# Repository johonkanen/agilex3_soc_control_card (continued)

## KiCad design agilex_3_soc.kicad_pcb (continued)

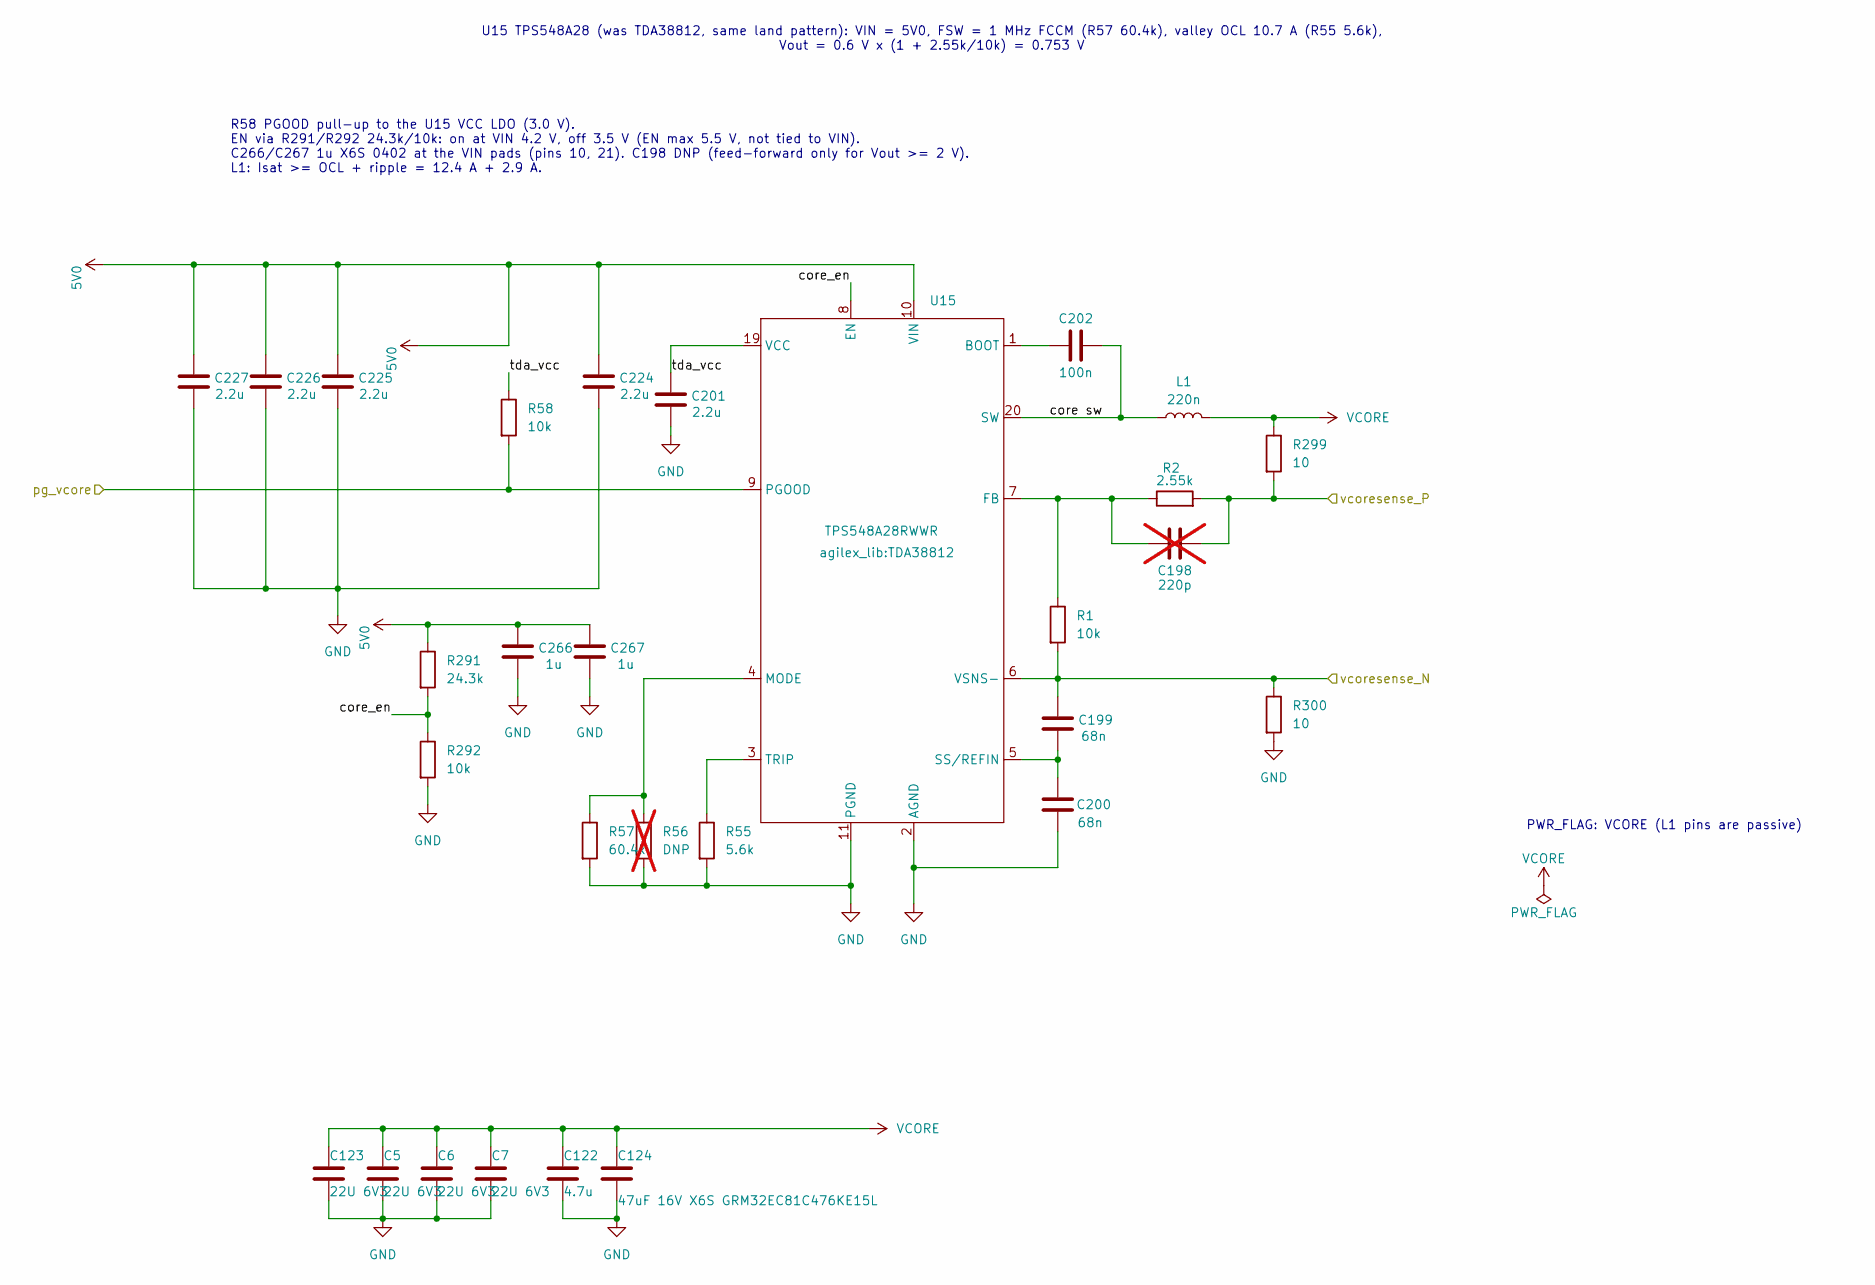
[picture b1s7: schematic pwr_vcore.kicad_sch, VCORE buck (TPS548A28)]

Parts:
C5, C6, C7, C123: 22U 6V3; C_0402_1005Metric; LCSC C415703
C122: 4.7u; C_0201_0603Metric; LCSC C5969171
C124: 47uF 16V X6S GRM32EC81C476KE15L; C_1210_3225Metric; LCSC C162512
C198: 220p; C_0402_1005Metric; LCSC C1530; not fitted
C199, C200: 68n; C_0402_1005Metric; LCSC C327019
C201, C224, C225, C226, C227: 2.2u; C_0402_1005Metric; LCSC C12530
C202: 100n; C_0402_1005Metric; LCSC C1525
C266, C267: 1u; C_0402_1005Metric; LCSC C393026
L1: 220n; L_TaiTech_TMPC0503H; LCSC C357176
R1, R58, R292: 10k; R_0402_1005Metric; LCSC C25744
R2: 2.55k; R_0402_1005Metric; LCSC C95596
R55: 5.6k; R_0402_1005Metric; LCSC C25908
R56: DNP; R_0402_1005Metric; not fitted
R57: 60.4k; R_0402_1005Metric; LCSC C25911
R291: 24.3k; R_0402_1005Metric; LCSC C26969
R299, R300: 10; R_0402_1005Metric; LCSC C25077
U15: TPS548A28RWWR; TDA38812; LCSC C5219375

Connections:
5V0: C224.2, C225.2, C226.2, C227.2, C266.2, C267.2, R291.1, U15.10 (VIN); also elsewhere on the board
/pwr_rails/EN: R58.2, U15.9 (PGOOD); also elsewhere on the board
/pwr_vcore/core sw: C202.2, L1.1, U15.20 (SW)
/pwr_vcore/core_en: R291.2, R292.1, U15.8 (EN)
/pwr_vcore/tda_vcc: C201.2, R58.1, U15.19 (VCC)
/pwr_vcore/vcoresense_N: C199.2, R1.2, R300.1, U15.6 (VSNS-); also elsewhere on the board
/soc_power/vcoresense_P: C198.2, R2.2, R299.2; also elsewhere on the board
GND: C5.2, C6.2, C7.2, C122.2, C123.2, C124.2, C200.1, C201.1, C224.1, C225.1, C226.1, C227.1, C266.1, C267.1, R55.2, R56.2, R57.2, R292.2, R300.2, U15.2 (AGND), U15.11 (PGND); also elsewhere on the board
unnamed: C202.1, U15.1 (BOOT)
unnamed: C198.1, R1.1, R2.1, U15.7 (FB)
unnamed: R56.1, R57.1, U15.4 (MODE)
unnamed: C199.1, C200.2, U15.5 (SS/REFIN)
unnamed: R55.1, U15.3 (TRIP)
VCORE: C5.1, C6.1, C7.1, C122.1, C123.1, C124.1, L1.2, R299.1; also elsewhere on the board

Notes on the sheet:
U15 TPS548A28 (was TDA38812, same land pattern): VIN = 5V0, FSW = 1 MHz FCCM (R57 60.4k), valley OCL 10.7 A (R55 5.6k), Vout = 0.6 V x (1 + 2.55k/10k) = 0.753 V
R58 PGOOD pull-up to the U15 VCC LDO (3.0 V). EN via R291/R292 24.3k/10k: on at VIN 4.2 V, off 3.5 V (EN max 5.5 V, not tied to VIN). C266/C267 1u X6S 0402 at the VIN pads (pins 10, 21). C198 DNP (feed-forward only for Vout >= 2 V). L1: Isat >= OCL + ripple = 12.4 A + 2.9 A.
PWR_FLAG: VCORE (L1 pins are passive)

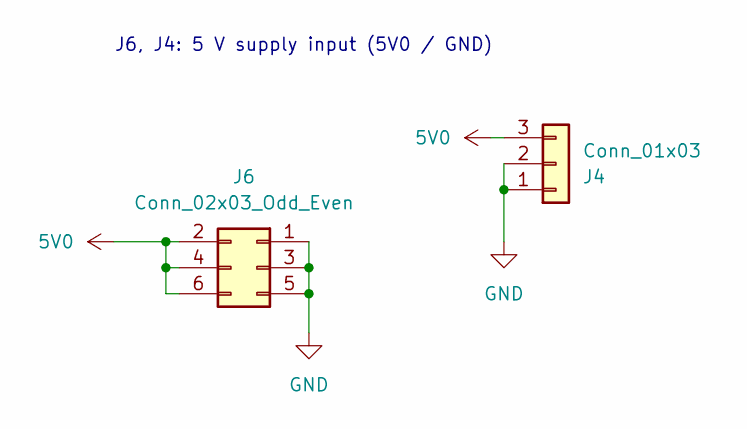
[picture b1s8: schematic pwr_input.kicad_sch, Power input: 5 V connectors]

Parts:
J4: Conn_01x03; PinHeader_1x03_P2.54mm_Vertical; LCSC C2937625
J6: Conn_02x03_Odd_Even; PinHeader_2x03_P1.27mm_Vertical; LCSC C22438118

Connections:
5V0: J4.3, J6.2, J6.4, J6.6; also elsewhere on the board
GND: J4.1, J4.2, J6.1, J6.3, J6.5; also elsewhere on the board

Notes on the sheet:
J6, J4: 5 V supply input (5V0 / GND)

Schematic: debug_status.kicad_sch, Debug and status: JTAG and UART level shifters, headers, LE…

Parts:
C253, C254, C273, C274: 100n; C_0402_1005Metric; LCSC C1525
D1, D2: KT-0603R; LED_0603_1608Metric; LCSC C2286
J1: Conn_01x05; PinHeader_1x05_P2.54mm_Vertical; LCSC C492404
J2: Conn_01x03; PinHeader_1x03_P2.54mm_Vertical; LCSC C2937625
J10: HPS_UART_3V3; PinHeader_1x02_P2.54mm_Vertical; LCSC C492401
R16, R17: 680R; R_0402_1005Metric; LCSC C25130
R47, R48: 10k; R_0402_1005Metric; LCSC C25744
R301: 4K7; R_0402_1005Metric; LCSC C25900
U1, U42: SN74AXC4T774PWR; TSSOP-16_4.4x5mm_P0.65mm; LCSC C1849453

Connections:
1V8: C253.1, C273.1, U1.15 (VCCB), U42.15 (VCCB); also elsewhere on the board
3V3: C254.1, C274.1, R47.1, R48.1, R301.1, U1.1 (DIR1), U1.2 (DIR2), U1.7 (DIR3), U1.16 (VCCA), U42.2 (DIR2), U42.16 (VCCA); also elsewhere on the board
/debug_status/hps_uart0_rx_3v3: J10.2, R301.2, U42.4 (A2)
/debug_status/hps_uart0_tx_3v3: J10.1, U42.3 (A1)
/debug_status/jtag_tck_3v3: J1.2, U1.4 (A2)
/debug_status/jtag_tdi_3v3: J1.1, U1.3 (A1)
/debug_status/jtag_tdo_3v3: J1.4, U1.6 (A4)
/debug_status/jtag_tms_3v3: J1.3, U1.5 (A3)
/debug_status/pg_all_3v3: R16.2, U42.6 (A4)
/eth_rst_n: U42.12 (B3); also elsewhere on the board
/fpga_bank6ab/iob6b8: J2.2, R47.2; also elsewhere on the board
/fpga_bank6ab/iob6b11: J2.1, R48.2; also elsewhere on the board
/fpga_led: R17.2; also elsewhere on the board
/hps_uart0_rx: U42.13 (B2); also elsewhere on the board
/hps_uart0_tx: U42.14 (B1); also elsewhere on the board
/pg_all: U42.11 (B4); also elsewhere on the board
/phy_rst_n: U42.5 (A3); also elsewhere on the board
/tck: U1.13 (B2); also elsewhere on the board
/tdi: U1.14 (B1); also elsewhere on the board
/tdo: U1.11 (B4); also elsewhere on the board
/tms: U1.12 (B3); also elsewhere on the board
GND: C253.2, C254.2, C273.2, C274.2, D1.1 (K), D2.1 (K), J1.5, J2.3, U1.8 (DIR4), U1.9 (OE), U1.10 (GND), U42.1 (DIR1), U42.7 (DIR3), U42.8 (DIR4), U42.9 (OE), U42.10 (GND); also elsewhere on the board
unnamed: D1.2 (A), R16.1
unnamed: D2.2 (A), R17.1

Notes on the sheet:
U42 SN74AXC4T774, 1.8 V (B) <-> 3.3 V (A): Ch1 DIR1 low = B->A: HPS UART0 TX out Ch2 DIR2 high = A->B: UART0 RX in Ch3: eth_rst_n -> phy_rst_n (PHY reset) Ch4 DIR4 low: pg_all (1.8 V) -> pg_all_3v3 -> LED D1
D2: user LED on FPGA IO CE6 (bank 6B, 3.3 V)
D1: power good (pg_all_3v3, from U42 ch4)
pg_all: regulator power-good wired-AND (ps1); also the PHY RESET_N pull-up (eth)
J10: 1 = TX (3.3 V out), 2 = RX (3.3 V in). GND on J2.3 / J4
UART RX idle pull-up (A2-03): U42 has 71k pull-downs, so RX reads as a break with no cable on J10.

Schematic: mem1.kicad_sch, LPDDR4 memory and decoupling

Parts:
C44, C47, C48: 22U 6V3; C_0402_1005Metric; LCSC C415703
C49, C50, C52, C53, C54, C56, C57, C58, C60, C61, C62, C63, C65, C66, C67, C69, C70, C71, C73, C74, C75, C77, C78, C79, C81, C82, C83, C85, C87, C89, C93: 100N; C_0201_0603Metric; LCSC C190183
C262, C263, C264, C265: 1u; C_0402_1005Metric; LCSC C52923
R43: 240R; R_0402_1005Metric; LCSC C25094
R44: 1K0; R_0402_1005Metric; LCSC C11702
U12: H9HCNNN8KUMLHR-NMO; BGA-200_10x15mm_Layout12x22_P0.8x0.65mm; LCSC C51891855

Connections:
1V1: C47.1, C49.1, C50.1, C53.1, C54.1, C57.1, C58.1, C61.1, C62.1, C63.1, C65.1, C66.1, C67.1, C69.1, C70.1, C71.1, C73.1, C74.1, C75.1, C77.1, C78.1, C79.1, C81.1, C82.1, C83.1, C85.1, C87.1, C89.1, C93.1, C262.1, C263.1, C264.1, C265.1, R43.2, U12.A4 (VDD2), U12.A9 (VDD2), U12.AA3 (VDDQ), U12.AA5 (VDDQ), U12.AA8 (VDDQ), U12.AA10 (VDDQ), U12.AB4 (VDD2), U12.AB9 (VDD2), U12.B3 (VDDQ), U12.B5 (VDDQ), U12.B8 (VDDQ), U12.B10 (VDDQ), U12.D1 (VDDQ), U12.D5 (VDDQ), U12.D8 (VDDQ), U12.D12 (VDDQ), U12.F3 (VDDQ), U12.F5 (VDD2), U12.F8 (VDD2), U12.F10 (VDDQ), U12.G2 (ODT_CA_A), U12.H1 (VDD2), U12.H5 (VDD2), U12.H8 (VDD2), U12.H12 (VDD2), U12.K1 (VDD2), U12.K3 (VDD2), U12.K10 (VDD2), U12.K12 (VDD2), U12.N1 (VDD2), U12.N3 (VDD2), U12.N10 (VDD2), U12.N12 (VDD2), U12.R1 (VDD2), U12.R5 (VDD2), U12.R8 (VDD2), U12.R12 (VDD2), U12.T2 (ODT_CA_B), U12.U3 (VDDQ), U12.U5 (VDD2), U12.U8 (VDD2), U12.U10 (VDDQ), U12.W1 (VDDQ), U12.W5 (VDDQ), U12.W8 (VDDQ), U12.W12 (VDDQ); also elsewhere on the board
1V8: C44.1, C48.1, C52.1, C56.1, C60.1, U12.F1 (VDD1), U12.F12 (VDD1), U12.G4 (VDD1), U12.G9 (VDD1), U12.T4 (VDD1), U12.T9 (VDD1), U12.U1 (VDD1), U12.U12 (VDD1); also elsewhere on the board
/IOBANK 3/ca0: U12.H2 (CA0_A), U12.R2 (CA0_B); also elsewhere on the board
/IOBANK 3/ca1: U12.J2 (CA1_A), U12.P2 (CA1_B); also elsewhere on the board
/IOBANK 3/ca2: U12.H9 (CA2_A), U12.R9 (CA2_B); also elsewhere on the board
/IOBANK 3/ca3: U12.H10 (CA3_A), U12.R10 (CA3_B); also elsewhere on the board
/IOBANK 3/ca4: U12.H11 (CA4_A), U12.R11 (CA4_B); also elsewhere on the board
/IOBANK 3/ca5: U12.J11 (CA5_A), U12.P11 (CA5_B); also elsewhere on the board
/IOBANK 3/ck_N: U12.J9 (CK_C_A), U12.P9 (CK_C_B); also elsewhere on the board
/IOBANK 3/ck_P: U12.J8 (CK_T_A), U12.P8 (CK_T_B); also elsewhere on the board
/IOBANK 3/cke: U12.J4 (CKE0_A), U12.P4 (CKE0_B); also elsewhere on the board
/IOBANK 3/dm0: U12.C3 (DMI0_A); also elsewhere on the board
/IOBANK 3/dm1: U12.C10 (DMI1_A); also elsewhere on the board
/IOBANK 3/dm2: U12.Y3 (DMI0_B); also elsewhere on the board
/IOBANK 3/dm3: U12.Y10 (DMI1_B); also elsewhere on the board
/IOBANK 3/dq0: U12.B2 (DQ0_A); also elsewhere on the board
/IOBANK 3/dq1: U12.C2 (DQ1_A); also elsewhere on the board
/IOBANK 3/dq2: U12.E2 (DQ2_A); also elsewhere on the board
/IOBANK 3/dq3: U12.F2 (DQ3_A); also elsewhere on the board
/IOBANK 3/dq4: U12.F4 (DQ4_A); also elsewhere on the board
/IOBANK 3/dq5: U12.E4 (DQ5_A); also elsewhere on the board
/IOBANK 3/dq6: U12.C4 (DQ6_A); also elsewhere on the board
/IOBANK 3/dq7: U12.B4 (DQ7_A); also elsewhere on the board
/IOBANK 3/dq8: U12.B11 (DQ8_A); also elsewhere on the board
/IOBANK 3/dq9: U12.C11 (DQ9_A); also elsewhere on the board
/IOBANK 3/dq10: U12.E11 (DQ10_A); also elsewhere on the board
/IOBANK 3/dq11: U12.F11 (DQ11_A); also elsewhere on the board
/IOBANK 3/dq12: U12.F9 (DQ12_A); also elsewhere on the board
/IOBANK 3/dq13: U12.E9 (DQ13_A); also elsewhere on the board
/IOBANK 3/dq14: U12.C9 (DQ14_A); also elsewhere on the board
/IOBANK 3/dq15: U12.B9 (DQ15_A); also elsewhere on the board
/IOBANK 3/dq16: U12.AA2 (DQ0_B); also elsewhere on the board
/IOBANK 3/dq17: U12.Y2 (DQ1_B); also elsewhere on the board
/IOBANK 3/dq18: U12.V2 (DQ2_B); also elsewhere on the board
/IOBANK 3/dq19: U12.U2 (DQ3_B); also elsewhere on the board
/IOBANK 3/dq20: U12.U4 (DQ4_B); also elsewhere on the board
/IOBANK 3/dq21: U12.V4 (DQ5_B); also elsewhere on the board
/IOBANK 3/dq22: U12.Y4 (DQ6_B); also elsewhere on the board
/IOBANK 3/dq23: U12.AA4 (DQ7_B); also elsewhere on the board
/IOBANK 3/dq24: U12.AA11 (DQ8_B); also elsewhere on the board
/IOBANK 3/dq25: U12.Y11 (DQ9_B); also elsewhere on the board
/IOBANK 3/dq26: U12.V11 (DQ10_B); also elsewhere on the board
/IOBANK 3/dq27: U12.U11 (DQ11_B); also elsewhere on the board
/IOBANK 3/dq28: U12.U9 (DQ12_B); also elsewhere on the board
/IOBANK 3/dq29: U12.V9 (DQ13_B); also elsewhere on the board
/IOBANK 3/dq30: U12.Y9 (DQ14_B); also elsewhere on the board
/IOBANK 3/dq31: U12.AA9 (DQ15_B); also elsewhere on the board
/IOBANK 3/dqs0_N: U12.E3 (DQS0_C_A); also elsewhere on the board
/IOBANK 3/dqs0_P: U12.D3 (DQS0_T_A); also elsewhere on the board
/IOBANK 3/dqs1_N: U12.E10 (DQS1_C_A); also elsewhere on the board
/IOBANK 3/dqs1_P: U12.D10 (DQS1_T_A); also elsewhere on the board
/IOBANK 3/dqs2_N: U12.V3 (DQS0_C_B); also elsewhere on the board
/IOBANK 3/dqs2_P: U12.W3 (DQS0_T_B); also elsewhere on the board
/IOBANK 3/dqs3_N: U12.V10 (DQS1_C_B); also elsewhere on the board
/IOBANK 3/dqs3_P: U12.W10 (DQS1_T_B); also elsewhere on the board
/IOBANK 3/~cs: U12.H4 (CS0_A), U12.R4 (CS0_B); also elsewhere on the board
/IOBANK 3/~rst: R44.1, U12.T11 (RESET_N); also elsewhere on the board
GND: C44.2, C47.2, C48.2, C49.2, C50.2, C52.2, C53.2, C54.2, C56.2, C57.2, C58.2, C60.2, C61.2, C62.2, C63.2, C65.2, C66.2, C67.2, C69.2, C70.2, C71.2, C73.2, C74.2, C75.2, C77.2, C78.2, C79.2, C81.2, C82.2, C83.2, C85.2, C87.2, C89.2, C93.2, C262.2, C263.2, C264.2, C265.2, R44.2, U12.A3 (VSS), U12.A10 (VSS), U12.AB3 (VSS), U12.AB5 (VSS), U12.AB8 (VSS), U12.AB10 (VSS), U12.C1 (VSS), U12.C5 (VSS), U12.C8 (VSS), U12.C12 (VSS), U12.D2 (VSS), U12.D4 (VSS), U12.D9 (VSS), U12.D11 (VSS), U12.E1 (VSS), U12.E5 (VSS), U12.E8 (VSS), U12.E12 (VSS), U12.G1 (VSS), U12.G3 (VSS), U12.G5 (VSS), U12.G8 (VSS), U12.G10 (VSS), U12.G12 (VSS), U12.J1 (VSS), U12.J3 (VSS), U12.J10 (VSS), U12.J12 (VSS), U12.K2 (VSS), U12.K4 (VSS), U12.K9 (VSS), U12.K11 (VSS), U12.N2 (VSS), U12.N4 (VSS), U12.N9 (VSS), U12.N11 (VSS), U12.P1 (VSS), U12.P3 (VSS), U12.P10 (VSS), U12.P12 (VSS), U12.T1 (VSS), U12.T3 (VSS), U12.T5 (VSS), U12.T8 (VSS), U12.T10 (VSS), U12.T12 (VSS), U12.V1 (VSS), U12.V5 (VSS), U12.V8 (VSS), U12.V12 (VSS), U12.W2 (VSS), U12.W4 (VSS), U12.W9 (VSS), U12.W11 (VSS), U12.Y1 (VSS), U12.Y5 (VSS), U12.Y8 (VSS), U12.Y12 (VSS); also elsewhere on the board
unnamed: R43.1, U12.A5 (ZQ0)

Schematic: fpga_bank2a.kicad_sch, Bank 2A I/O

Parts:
R24: 240R; R_0402_1005Metric; LCSC C25094
U7: A5EB013B-B23B; Altera_B23B

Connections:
/fpga_bank2a/rzq_b_2a: R24.1, U7.DP58 (2A_B_IO38_IOB_RZQ_B_2A_DIFF_IO_2A_B5p)
GND: R24.2; also elsewhere on the board

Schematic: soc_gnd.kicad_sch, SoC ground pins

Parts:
U7: A5EB013B-B23B; Altera_B23B

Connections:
/pwr_vcore/vcoresense_N: U7.BN44 (GNDSENSE); also elsewhere on the board
GND: U7.A3 (GND), U7.A5 (GND), U7.A17 (GND), U7.A28 (GND), U7.A41 (GND), U7.A53 (GND), U7.A63 (GND), U7.A73 (GND), U7.A74 (GND), U7.AA72 (GND), U7.AB27 (GND), U7.AB35 (GND), U7.AB42 (GND), U7.AB51 (GND), U7.AB59 (GND), U7.AB65 (GND), U7.AE4 (GND), U7.AE16 (GND), U7.AF2 (GND), U7.AF74 (GND), U7.AG34 (GND), U7.AG44 (GND), U7.AG49 (GND), U7.AG52 (GND), U7.AG54 (GND), U7.AG57 (GND), U7.AG60 (GND), U7.AH8 (GND), U7.AK64 (GND), U7.AK72 (GND), U7.AL23 (GND), U7.AL26 (GND), U7.AL40 (GND), U7.AL44 (GND), U7.AL49 (GND), U7.AL57 (GND), U7.AL60 (GND), U7.AM1 (GND), U7.AM75 (GND), U7.AN69 (GND), U7.AR29 (GND), U7.AR44 (GND), U7.AR46 (GND), U7.AR54 (GND), U7.AR60 (GND), U7.AT4 (GND), U7.AT16 (GND), U7.AV8 (GND), U7.AW26 (GND), U7.AW37 (GND), U7.AW44 (GND), U7.AW52 (GND), U7.AW54 (GND), U7.AW60 (GND), U7.AY64 (GND), U7.AY72 (GND), U7.B13 (GND), U7.B20 (GND), U7.B23 (GND), U7.B36 (GND), U7.B47 (GND), U7.B60 (GND), U7.B70 (GND), U7.B75 (GND), U7.BA2 (GND), U7.BA74 (GND), U7.BB23 (GND), U7.BB31 (GND), U7.BB40 (GND), U7.BB49 (GND), U7.BB57 (GND), U7.BB60 (GND), U7.BC69 (GND), U7.BE4 (GND), U7.BE16 (GND), U7.BF29 (GND), U7.BF37 (GND), U7.BF46 (GND), U7.BF54 (GND), U7.BF60 (GND), U7.BG1 (GND), U7.BG75 (GND), U7.BH8 (GND), U7.BJ34 (GND), U7.BJ44 (GND), U7.BJ52 (GND), U7.BJ57 (GND), U7.BK64 (GND), U7.BK72 (GND), U7.BM64 (GND), U7.BM67 (GND), U7.BM69 (GND), U7.BN23 (GND), U7.BN31 (GND), U7.BN40 (GND), U7.BN49 (GND), U7.BN57 (GND), U7.BR4 (GND), U7.BR16 (GND), U7.BT2 (GND), U7.BT74 (GND), U7.BU29 (GND), U7.BU37 (GND), U7.BU46 (GND), U7.BU54 (GND), U7.BU57 (GND), U7.BU60 (GND), U7.BV8 (GND), U7.BY64 (GND), U7.BY72 (GND), U7.C1 (GND), U7.C4 (GND), U7.C16 (GND), U7.C75 (GND), U7.CA26 (GND), U7.CA34 (GND), U7.CA44 (GND), U7.CA52 (GND), U7.CA60 (GND), U7.CB1 (GND), U7.CB75 (GND), U7.CC69 (GND), U7.CD31 (GND), U7.CD40 (GND), U7.CD49 (GND), U7.CD57 (GND), U7.CE4 (GND), U7.CE16 (GND), U7.CG29 (GND), U7.CG37 (GND), U7.CG46 (GND), U7.CG54 (GND), U7.CH8 (GND), U7.CK64 (GND), U7.CK72 (GND), U7.CL23 (GND), U7.CL26 (GND), U7.CL34 (GND), U7.CL44 (GND), U7.CL52 (GND), U7.CL60 (GND), U7.CM2 (GND), U7.CM74 (GND), U7.CN69 (GND), U7.CR4 (GND), U7.CR16 (GND), U7.CT31 (GND), U7.CT40 (GND), U7.CT49 (GND), U7.CT57 (GND), U7.CU1 (GND), U7.CU74 (GND), U7.CU75 (GND), U7.CV8 (GND), U7.CW29 (GND), U7.CW37 (GND), U7.CW46 (GND), U7.CW54 (GND), U7.CY64 (GND), U7.CY72 (GND), U7.D72 (GND), U7.DE2 (GND), U7.DE74 (GND), U7.DF9 (GND), U7.DF18 (GND), U7.DF24 (GND), U7.DF32 (GND), U7.DF39 (GND), U7.DF48 (GND), U7.DF56 (GND), U7.DF62 (GND), U7.DG72 (GND), U7.DK3 (GND), U7.DK12 (GND), U7.DK21 (GND), U7.DK27 (GND), U7.DK35 (GND), U7.DK42 (GND), U7.DK51 (GND), U7.DK59 (GND), U7.DK65 (GND), U7.DL72 (GND), U7.DM1 (GND), U7.DM74 (GND), U7.DM75 (GND), U7.DN1 (GND), U7.DN13 (GND), U7.DN23 (GND), U7.DN36 (GND), U7.DN47 (GND), U7.DN60 (GND), U7.DN70 (GND), U7.DN75 (GND), U7.DP2 (GND), U7.DP3 (GND), U7.DP17 (GND), U7.DP28 (GND), U7.DP41 (GND), U7.DP53 (GND), U7.DP63 (GND), U7.DP73 (GND), U7.DP74 (GND), U7.E27 (GND), U7.E35 (GND), U7.E42 (GND), U7.E51 (GND), U7.E59 (GND), U7.E65 (GND), U7.F1 (GND), U7.H8 (GND), U7.J24 (GND), U7.J32 (GND), U7.J39 (GND), U7.J48 (GND), U7.J56 (GND), U7.J62 (GND), U7.K72 (GND), U7.L2 (GND), U7.L74 (GND), U7.R4 (GND), U7.R16 (GND), U7.U1 (GND), U7.U75 (GND), U7.V8 (GND), U7.W27 (GND), U7.W35 (GND), U7.W42 (GND), U7.W51 (GND), U7.W59 (GND), U7.W65 (GND); also elsewhere on the board

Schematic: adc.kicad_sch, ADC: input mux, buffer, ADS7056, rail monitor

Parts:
C1: 4u7; C_0603_1608Metric; LCSC C19666
C2, C4: 100n; C_0402_1005Metric; LCSC C1525
C3: 680p; C_0402_1005Metric; LCSC C113781
C261: 1u; C_0402_1005Metric; LCSC C52923
R3, R265, R266, R267: 33R; R_0402_1005Metric; LCSC C25105
R5: 100; R_0402_1005Metric; LCSC C25076
R42, R46, R51, R53, R54: 1k; R_0402_1005Metric; LCSC C11702
U3: TMUX1308PWR; TSSOP-16_4.4x5mm_P0.65mm; LCSC C970231
U4: OPA365AIDBVR; SOT-23-5; LCSC C96626
U5: ADS7056IRUGR; ads7056; LCSC C2669798

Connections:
1V1: R46.1; also elsewhere on the board
1V2: R54.1; also elsewhere on the board
1V8: R53.1; also elsewhere on the board
3V3: C261.1, R42.1, U5.4 (DVDD); also elsewhere on the board
3V3_analog: C1.1, C2.1, C4.1, U3.16 (VDD), U4.5 (V+), U5.6 (AVDD); also elsewhere on the board
/ad_ch0: R5.2, U3.13 (X0)
/ad_ch1: R42.2, R51.1, U3.14 (X1)
/ad_ch2: R53.2, U3.15 (X2)
/ad_ch3: R54.2, U3.12 (X3)
/ad_ch4: U3.1 (X4); also elsewhere on the board
/ad_ch5: R46.2, U3.5 (X5)
/ad_ch6: U3.2 (X6); also elsewhere on the board
/ad_ch7: U3.4 (X7); also elsewhere on the board
/fpga_bank6ab/iob6b5: U3.9 (C); also elsewhere on the board
/fpga_bank6ef/iob6f3: R265.2; also elsewhere on the board
/fpga_bank6ef/iob6f6: R267.2; also elsewhere on the board
/fpga_bank6ef/iob6f7: R266.2; also elsewhere on the board
/fpga_bank6ef/iob6f8: U3.11 (A); also elsewhere on the board
/fpga_bank6ef/iob6f9: U3.10 (B); also elsewhere on the board
GND: C1.2, C2.2, C3.2, C4.2, C261.2, R51.2, U3.6 (INH), U3.7 (VEE), U3.8 (VSS), U4.2 (V-), U5.5 (GND), U5.8 (AINM); also elsewhere on the board
unnamed: U3.3 (X), U4.3 (+)
unnamed: R3.1, U4.1, U4.4 (-)
unnamed: C3.1, R3.2, U5.7 (AINP)
unnamed: R266.1, U5.3 (SCLK)
unnamed: R265.1, U5.2 (SDO)
unnamed: R267.1, U5.1 (~CS)
VCORE: R5.1; also elsewhere on the board

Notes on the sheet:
R265-R267: 33R series on SDO/SCLK/CS (SCLK up to 60 MHz), as on the Agilex 3 card. Front end per ADS7056 data sheet 9.2.1: OPA365 + 33R/680p C0G, AVDD (= reference) 4u7 at the pin, DVDD on digital 3V3.
Rail monitor: ad_ch0 VCORE, ad_ch1 3V3 / 2, ad_ch2 1V8, ad_ch3 1V2, ad_ch5 1V1. ad_ch4, ad_ch6, ad_ch7 come from header J3.

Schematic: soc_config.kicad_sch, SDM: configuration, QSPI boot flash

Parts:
R4, R7, R45: 4K7; R_0402_1005Metric; LCSC C25900
R8, R11, R12, R14, R15, R19, R20, R21, R264: 10K; R_0402_1005Metric; LCSC C25744
R9, R10: 10K; R_0402_1005Metric; LCSC C25744; not fitted
R18: 2K0; R_0402_1005Metric; LCSC C4109
R22: 1K0; R_0402_1005Metric; LCSC C11702
R293, R294, R295, R296, R297, R298: 22R; R_0201_0603Metric; LCSC C155743
U2: IS25WP128-RHLE; MX25U25645G_CSP24_6x8mm_P1.0mm; LCSC C1349419
U7: A5EB013B-B23B; Altera_B23B

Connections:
1V8: R7.1, R8.1, R9.1, R10.1, R11.1, R12.1, R14.1, R15.1, R19.1, R20.1, R21.1, R45.2, R264.1, U2.B4 (VCC); also elsewhere on the board
/sdm_clk25: U7.DB72 (SDM_OSC_CLK_1); also elsewhere on the board
/soc_config/conf_done: R10.2, U7.DA74 (SDM_SDM_IO16_PWRMGT_SDA)
/soc_config/hps_cold_rst_n: R264.2, U7.CK69 (SDM_SDM_IO10_AVSTx8_DATA7)
/soc_config/init_done: R9.2, U7.BK67 (SDM_SDM_IO0_PWRMGT_SCL_PWRMGT_ALERT)
/soc_config/msel1: R45.1, U7.CN67 (SDM_SDM_IO7_AS_nCSO2_MSEL1)
/soc_config/msel2: R4.1, U7.CN71 (SDM_SDM_IO9_AS_nCSO1_MSEL2_PWRMGT_ALERT)
/soc_config/qspi_CLK: R293.1, U2.B2 (SCLK)
/soc_config/qspi_CLK_sdm: R293.2, U7.CY69 (SDM_SDM_IO2_AVSTx8_DATA0_AS_CLK)
/soc_config/qspi_D0: R295.1, U2.D3 (SI/SIO0)
/soc_config/qspi_D0_sdm: R295.2, U7.CN64 (SDM_SDM_IO4_AVSTx8_DATA1_AS_DATA0)
/soc_config/qspi_D1: R296.1, U2.D2 (SO/SIO1)
/soc_config/qspi_D1_sdm: R296.2, U7.CK67 (SDM_SDM_IO1_AVSTx8_DATA2_AS_DATA1)
/soc_config/qspi_D2: R12.2, R297.1, U2.C4 (WP#/SIO2)
/soc_config/qspi_D2_sdm: R297.2, U7.DC74 (SDM_SDM_IO3_AVSTx8_DATA3_AS_DATA2)
/soc_config/qspi_D3: R14.2, R298.1, U2.D4 (NC/SIO3)
/soc_config/qspi_D3_sdm: R298.2, U7.DC75 (SDM_SDM_IO6_AVSTx8_DATA4_AS_DATA3)
/soc_config/~nconfig: R8.2, U7.BK71 (SDM_nCONFIG)
/soc_config/~nstatus: R11.2, U7.BM71 (SDM_nSTATUS)
/soc_config/~qspi_CS_sdm: R7.2, R294.2, U7.BY71 (SDM_SDM_IO5_AS_nCSO0_MSEL0)
/soc_config/~qspi_CS: R294.1, U2.C2 (CS#)
/soc_config/~qspi_rst_n: R15.2, U2.A4 (RESET#), U7.CY71 (SDM_SDM_IO15_AVSTx8_DATA6_AS_nRST)
/tck: R22.2, U7.CC64 (SDM_TCK); also elsewhere on the board
/tdi: R19.2, U7.CC67 (SDM_TDI); also elsewhere on the board
/tdo: R20.2, U7.BY67 (SDM_TDO); also elsewhere on the board
/tms: R21.2, U7.CY67 (SDM_TMS); also elsewhere on the board
GND: R4.2, R18.2, R22.1, U2.B3 (GND), U7.BW74 (SDM_VSIGN_0), U7.BW75 (SDM_VSIGP_0), U7.CF74 (SDM_VREFN_ADC), U7.CF75 (SDM_VREFP_ADC), U7.CJ74 (SDM_VSIGP_1), U7.CJ75 (SDM_VSIGN_1); also elsewhere on the board
unnamed: R18.1, U7.DH75 (SDM_RREF_SDM)

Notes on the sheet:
msel0
SDM_IO13 unused
R264: HPS_COLD_nRESET pull-up, 1-10k to VCCIO_SDM (PCG 813266). MSEL = 011 (AS normal): R45 to 1V8. R9/R10 DNP: SDM_IO0/IO16 have internal pull-downs.

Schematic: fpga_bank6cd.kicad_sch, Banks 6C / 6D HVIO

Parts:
U7: A5EB013B-B23B; Altera_B23B

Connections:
/fpga_bank6cd/iob6c1: U7.H11 (6C_IO_HVIO_6C_14_TXCLK14_Data_Ctrl14)
/fpga_bank6cd/iob6c2: U7.H14 (6C_IO_HVIO_6C_12_SOURCE_SYNC_CLK2_TXCLK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)
/fpga_bank6cd/iob6d0: U7.Y2 (6D_IO_HVIO_6D_5_TXCLK5_Data_Ctrl5); also elsewhere on the board
/fpga_bank6cd/iob6d1: U7.Y1 (6D_IO_HVIO_6D_2_TXCLK2_Data_Ctrl2); also elsewhere on the board
/fpga_bank6cd/iob6d2: U7.U2 (6D_IO_HVIO_6D_1_TXCLK1_Data_Ctrl1); also elsewhere on the board
/fpga_bank6cd/iob6d3: U7.P2 (6D_IO_HVIO_6D_4_TXCLK4_Data_Ctrl4); also elsewhere on the board
/fpga_bank6cd/iob6d4: U7.P1 (6D_IO_HVIO_6D_3_TXCLK3_Data_Ctrl3); also elsewhere on the board
/fpga_bank6cd/iob6d9: U7.C2 (6D_IO_HVIO_6D_9_PLLREFCLK1_TXCLK9_RXCLK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); also elsewhere on the board

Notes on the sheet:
VCCIO_6C : 3V3

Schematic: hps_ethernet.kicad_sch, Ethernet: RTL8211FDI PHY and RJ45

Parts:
C21, C258: 1u; C_0201_0603Metric; LCSC C272877
C22, C23, C25, C26, C28, C29, C30, C257: 100N; C_0201_0603Metric; LCSC C190183
C24: 22U 6V3; C_0402_1005Metric; LCSC C415703
C251, C252: 15p; C_0201_0603Metric; LCSC C161407
C255: 100n; C_0201_0603Metric; LCSC C190183
C259: 1u; C_0201_0603Metric; LCSC C272877; not fitted
FB1: BLM15PX121SZ1D; L_0402_1005Metric; LCSC C701266
J9: HR911130A; RJ45_Hanrun_HR911130A_Horizontal; LCSC C54408
R30, R31, R32, R33, R35, R39, R40, R268, R269, R270, R271: 4K7; R_0201_0603Metric; LCSC C270346
R36: 1K5; R_0201_0603Metric; LCSC C270361
R41: 2K49; R_0201_0603Metric; LCSC C473476
R247: 4.7k; R_0201_0603Metric; LCSC C270346
R250: 330R; R_0201_0603Metric; LCSC C516485
R251, R252, R253, R254, R255, R256, R257, R258, R259, R260, R261, R262: 22R; R_0201_0603Metric; LCSC C155743
U10: RTL8211FDI-CG; QFN-40-1EP_5x5mm_P0.4mm_EP3.6x3.6mm; LCSC C692886
Y3: 25MHz; Crystal_SMD_3225-4Pin_3.2x2.5mm; LCSC C9006

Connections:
1V8: R36.1, R40.1; also elsewhere on the board
3V3: C26.1, FB1.2, R250.2, R268.1, U10.29 (DVDD33); also elsewhere on the board
/eth_rst_n: C259.1, R247.1; also elsewhere on the board
/hps_ethernet/eth_ct: C255.1, J9.1 (TCT)
/hps_ethernet/eth_led_a: J9.11 (LEDG_A), R250.1
/hps_ethernet/eth_led_g_n: J9.12 (LEDG_K), R268.2, U10.34 (LED2/CFG_LDO1)
/hps_ethernet/phy_led1: R35.1, U10.33 (LED1/CFG_LDO0)
/hps_ethernet/txrxa_N: J9.3 (MDI0-), U10.2 (MDIN0)
/hps_ethernet/txrxa_P: J9.2 (MDI0+), U10.1 (MDIP0)
/hps_ethernet/txrxb_N: J9.7 (MDI1-), U10.5 (MDIN1)
/hps_ethernet/txrxb_P: J9.4 (MDI1+), U10.4 (MDIP1)
/hps_ethernet/txrxc_N: J9.6 (MDI2-), U10.7 (MDIN2)
/hps_ethernet/txrxc_P: J9.5 (MDI2+), U10.6 (MDIP2)
/hps_ethernet/txrxd_N: J9.9 (MDI3-), U10.10 (MDIN3)
/hps_ethernet/txrxd_P: J9.8 (MDI3+), U10.9 (MDIP3)
/hps_io/eth_gtx_clk: R256.1; also elsewhere on the board
/hps_io/eth_mdc: R40.2, U10.13 (MDC); also elsewhere on the board
/hps_io/eth_mdio: R36.2, U10.14 (MDIO); also elsewhere on the board
/hps_io/eth_rx_clk: R33.1, R262.1; also elsewhere on the board
/hps_io/eth_rx_dv: R31.1, R257.1; also elsewhere on the board
/hps_io/eth_rxd0: R39.2, R258.1; also elsewhere on the board
/hps_io/eth_rxd1: R259.1, R270.1; also elsewhere on the board
/hps_io/eth_rxd2: R260.1, R269.1; also elsewhere on the board
/hps_io/eth_rxd3: R32.2, R261.1; also elsewhere on the board
/hps_io/eth_tx_en: R251.1; also elsewhere on the board
/hps_io/eth_txd0: R252.1; also elsewhere on the board
/hps_io/eth_txd1: R253.1; also elsewhere on the board
/hps_io/eth_txd2: R254.1; also elsewhere on the board
/hps_io/eth_txd3: R255.1; also elsewhere on the board
/hps_io/~eth_int: R30.2, U10.31 (INTB/PMEB); also elsewhere on the board
/phy_rst_n: U10.12 (PHYRSTB); also elsewhere on the board
GND: C21.2, C22.2, C23.2, C24.2, C25.2, C26.2, C28.2, C29.2, C30.2, C251.2, C252.2, C255.2, C257.2, C258.2, C259.2, J9.10 (CHS), J9.SH (SHIELD), R31.2, R33.2, R35.2, R41.2, R247.2, R269.2, R270.2, R271.2, U10.41 (GND), Y3.2 (GND), Y3.4 (GND); also elsewhere on the board
unnamed: R271.1, U10.32 (LED0/CFG_EXT)
unnamed: R41.1, U10.39 (RSET)
unnamed: R257.2, U10.26 (RXCTL/PHYAD2)
unnamed: R262.2, U10.27 (RXC/PHYAD1)
unnamed: R258.2, U10.25 (RXD0/RXDLY)
unnamed: R259.2, U10.24 (RXD1/TXDLY)
unnamed: R260.2, U10.23 (RXD2/PLLOFF)
unnamed: R261.2, U10.22 (RXD3/PHYAD0)
unnamed: R256.2, U10.20 (TXC)
unnamed: R251.2, U10.19 (TXCTL)
unnamed: R252.2, U10.18 (TXD0)
unnamed: R253.2, U10.17 (TXD1)
unnamed: R254.2, U10.16 (TXD2)
unnamed: R255.2, U10.15 (TXD3)
unnamed: C251.1, U10.36 (XTAL_IN), Y3.1
unnamed: C252.1, U10.37 (XTAL_OUT), Y3.3 (2)
PHY1V0: C21.1, C22.1, C23.1, C28.1, C30.1, U10.3 (AVDD10), U10.8 (AVDD10), U10.21 (DVDD10), U10.30 (LDO_OUT), U10.38 (AVDD10)
PHY3V3: C24.1, C25.1, C29.1, FB1.1, U10.11 (AVDD33), U10.40 (AVDD33)
PHY_RG: C257.1, C258.1, R30.1, R32.1, R39.1, U10.28 (DVDD_RG)

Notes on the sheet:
25 MHz +/-50 ppm crystal (RTL8211FDI: +/-50 ppm incl. first-year aging and load caps). C251/C252 = 2*(CL - Cstray): 27p for CL=18pF; adjust to the crystal.
DVDD_RG decoupling C256-C258: pin 28 = internal 1.8 V RGMII/MDIO I/O LDO output (CFG_LDO=10), caps only.
U10 RTL8211FDI-CG (replaces KSZ9031RNX; JLC stock). Configured over MDIO; all nine CONFIG pins have external 4K7 pulls as data sheet 7.8 requires (see the strap note below): PHY address 1, PLLOFF=0, TXDLY=0, RXDLY=1, CFG_EXT=0, CFG_LDO=10 -> internal RGMII/MDIO I/O LDO at 1.8 V. Set RGMII delays in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
J9: HanRun HR911130A (LCSC C54408, as on the Zynq board). TCT (1) = PHY-side centre taps, all 4 pairs -> C255 100n to GND. CHS (10) and shield -> GND. Green LED 11(+)/12 <- PHY LED2 (1000M link/act, active low, 3.3 V, R250 330R); R268 is also the CFG_LDO1 strap. Yellow LED 13/14 unused.
RGMII series 22R: R251-R256 (TX, HPS -> PHY) place at the HPS end, R257-R262 (RX) at U10.
No trace delay. Strap defaults RXDLY=1 / TXDLY=0 until software sets them.
PWR_FLAG: PHY3V3 behind FB1
FB1: AVDD33 (pins 11, 40) filtered from 3V3. PHY1V0 = LDO_OUT (pin 30) -> AVDD10/DVDD10 only.
Optional at these lengths (<20 mm) - fit 0R if not wanted.
RGMII delay: set over MDIO (page 0xd08); with Linux phy-mode = "rgmii-id" the PHY adds 2 ns on TX and RX.
Config straps (data sheet 7.8: external pulls required), 4K7: PHYAD[2:0]=001 (R32 up / R33, R31 down), PLLOFF=0 (R269 down), TXDLY=0 (R270 down), RXDLY=1 (R39 up) - RX straps to PHY_RG; CFG_EXT=0 (R271 down on LED0), CFG_LDO=10 (R35 down on LED1, R268 up to 3V3 on LED2). R34/R37 DNP (wrong directio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
RESET: R247 10k pull-down + C259 1u on eth_rst_n (HPS GPIO1_IO18, K71, 1.8 V) -> U42 ch3 -> phy_rst_n (3.3 V) -> PHYRSTB. PHY held in reset until software drives the GPIO high; hold low >= 10 ms, wait >= 50 ms before MDIO access.

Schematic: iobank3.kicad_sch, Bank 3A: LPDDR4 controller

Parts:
R23, R248: 240R; R_0402_1005Metric; LCSC C25094
U7: A5EB013B-B23B; Altera_B23B

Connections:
/IOBANK 3/ca0: U7.B66 (3A_B_IO24_IOB_DIFF_IO_3A_B12p); also elsewhere on the board
/IOBANK 3/ca1: U7.A68 (3A_B_IO25_IOB_DIFF_IO_3A_B12n); also elsewhere on the board
/IOBANK 3/ca2: U7.B68 (3A_B_IO26_IOB_DIFF_IO_3A_B11p); also elsewhere on the board
/IOBANK 3/ca3: U7.A70 (3A_B_IO27_IOB_DIFF_IO_3A_B11n); also elsewhere on the board
/IOBANK 3/ca4: U7.B63 (3A_B_IO28_IOB_DIFF_IO_3A_B10p); also elsewhere on the board
/IOBANK 3/ca5: U7.A66 (3A_B_IO29_IOB_DIFF_IO_3A_B10n); also elsewhere on the board
/IOBANK 3/ck_N: U7.G42 (3A_B_IO43_IOB_DIFF_IO_3A_B3n); also elsewhere on the board
/IOBANK 3/ck_P: U7.J42 (3A_B_IO42_IOB_DIFF_IO_3A_B3p); also elsewhere on the board
/IOBANK 3/cke: U7.A61 (3A_B_IO30_IOB); also elsewhere on the board
/IOBANK 3/dm0: U7.T59 (3A_B_IO18_IOB_DIFF_IO_3A_B15p); also elsewhere on the board
/IOBANK 3/dm1: U7.J59 (3A_B_IO6_IOB_DIFF_IO_3A_B21p); also elsewhere on the board
/IOBANK 3/dm2: U7.A25 (3A_T_IO90_IOB_DIFF_IO_3A_T3p); also elsewhere on the board
/IOBANK 3/dm3: U7.J27 (3A_T_IO78_IOB_DIFF_IO_3A_T9p); also elsewhere on the board
/IOBANK 3/dq0: U7.M65 (3A_B_IO15_IOB_DIFF_IO_3A_B17n); also elsewhere on the board
/IOBANK 3/dq1: U7.T51 (3A_B_IO22_IOB_DIFF_IO_3A_B13p); also elsewhere on the board
/IOBANK 3/dq2: U7.W48 (3A_B_IO21_IOB_DIFF_IO_3A_B14n); also elsewhere on the board
/IOBANK 3/dq3: U7.AB48 (3A_B_IO20_IOB_DIFF_IO_3A_B14p); also elsewhere on the board
/IOBANK 3/dq4: U7.M51 (3A_B_IO23_IOB_DIFF_IO_3A_B13n); also elsewhere on the board
/IOBANK 3/dq5: U7.AB62 (3A_B_IO12_IOB_DIFF_IO_3A_B18p); also elsewhere on the board
/IOBANK 3/dq6: U7.W62 (3A_B_IO13_IOB_DIFF_IO_3A_B18n); also elsewhere on the board
/IOBANK 3/dq7: U7.T65 (3A_B_IO14_IOB_DIFF_IO_3A_B17p); also elsewhere on the board
/IOBANK 3/dq8: U7.G65 (3A_B_IO1_IOB_DIFF_IO_3A_B24n); also elsewhere on the board
/IOBANK 3/dq9: U7.E56 (3A_B_IO11_IOB_DIFF_IO_3A_B19n); also elsewhere on the board
/IOBANK 3/dq10: U7.J65 (3A_B_IO0_IOB_DIFF_IO_3A_B24p); also elsewhere on the board
/IOBANK 3/dq11: U7.M56 (3A_B_IO9_IOB_DIFF_IO_3A_B20n); also elsewhere on the board
/IOBANK 3/dq12: U7.T56 (3A_B_IO8_IOB_DIFF_IO_3A_B20p); also elsewhere on the board
/IOBANK 3/dq13: U7.T62 (3A_B_IO2_IOB_DIFF_IO_3A_B23p); also elsewhere on the board
/IOBANK 3/dq14: U7.M62 (3A_B_IO3_IOB_DIFF_IO_3A_B23n); also elsewhere on the board
/IOBANK 3/dq15: U7.G56 (3A_B_IO10_IOB_DIFF_IO_3A_B19p); also elsewhere on the board
/IOBANK 3/dq16: U7.A20 (3A_T_IO95_IOB_DIFF_IO_3A_T1n); also elsewhere on the board
/IOBANK 3/dq17: U7.A23 (3A_T_IO93_IOB_DIFF_IO_3A_T2n); also elsewhere on the board
/IOBANK 3/dq18: U7.A33 (3A_T_IO87_IOB_DIFF_IO_3A_T5n); also elsewhere on the board
/IOBANK 3/dq19: U7.A36 (3A_T_IO85_IOB_DIFF_IO_3A_T6n); also elsewhere on the board
/IOBANK 3/dq20: U7.B33 (3A_T_IO84_IOB_DIFF_IO_3A_T6p); also elsewhere on the board
/IOBANK 3/dq21: U7.B30 (3A_T_IO86_IOB_DIFF_IO_3A_T5p); also elsewhere on the board
/IOBANK 3/dq22: U7.A22 (3A_T_IO92_IOB_DIFF_IO_3A_T2p); also elsewhere on the board
/IOBANK 3/dq23: U7.B22 (3A_T_IO94_IOB_DIFF_IO_3A_T1p); also elsewhere on the board
/IOBANK 3/dq24: U7.G24 (3A_T_IO82_IOB_DIFF_IO_3A_T7p); also elsewhere on the board
/IOBANK 3/dq25: U7.E24 (3A_T_IO83_IOB_DIFF_IO_3A_T7n); also elsewhere on the board
/IOBANK 3/dq26: U7.G35 (3A_T_IO73_IOB_DIFF_IO_3A_T12n); also elsewhere on the board
/IOBANK 3/dq27: U7.J35 (3A_T_IO72_IOB_DIFF_IO_3A_T12p); also elsewhere on the board
/IOBANK 3/dq28: U7.M32 (3A_T_IO75_IOB_DIFF_IO_3A_T11n); also elsewhere on the board
/IOBANK 3/dq29: U7.T32 (3A_T_IO74_IOB_DIFF_IO_3A_T11p); also elsewhere on the board
/IOBANK 3/dq30: U7.M24 (3A_T_IO81_IOB_DIFF_IO_3A_T8n); also elsewhere on the board
/IOBANK 3/dq31: U7.T24 (3A_T_IO80_IOB_DIFF_IO_3A_T8p); also elsewhere on the board
/IOBANK 3/dqs0_N: U7.W56 (3A_B_IO17_IOB_DIFF_IO_3A_B16n); also elsewhere on the board
/IOBANK 3/dqs0_P: U7.AB56 (3A_B_IO16_IOB_DIFF_IO_3A_B16p); also elsewhere on the board
/IOBANK 3/dqs1_N: U7.E62 (3A_B_IO5_IOB_DIFF_IO_3A_B22n); also elsewhere on the board
/IOBANK 3/dqs1_P: U7.G62 (3A_B_IO4_IOB_DIFF_IO_3A_B22p); also elsewhere on the board
/IOBANK 3/dqs2_N: U7.A30 (3A_T_IO89_IOB_DIFF_IO_3A_T4n); also elsewhere on the board
/IOBANK 3/dqs2_P: U7.B28 (3A_T_IO88_IOB_DIFF_IO_3A_T4p); also elsewhere on the board
/IOBANK 3/dqs3_N: U7.E32 (3A_T_IO77_IOB_DIFF_IO_3A_T10n); also elsewhere on the board
/IOBANK 3/dqs3_P: U7.G32 (3A_T_IO76_IOB_DIFF_IO_3A_T10p); also elsewhere on the board
/IOBANK 3/rzq_b_3a: R23.1, U7.T48 (3A_B_IO38_IOB_RZQ_B_3A_DIFF_IO_3A_B5p)
/IOBANK 3/rzq_t_3a: R248.2, U7.M42 (3A_T_IO62_IOB_RZQ_T_3A_DIFF_IO_3A_T17p)
/IOBANK 3/~cs: U7.B58 (3A_B_IO32_IOB_DIFF_IO_3A_B8p); also elsewhere on the board
/IOBANK 3/~rst: U7.M48 (3A_B_IO39_IOB_DIFF_IO_3A_B5n); also elsewhere on the board
/iob3A_refclk_N: U7.A58 (3A_B_IO35_IOB_CLK_B_3A_0n_DIFF_IO_3A_B7n); also elsewhere on the board
/iob3A_refclk_P: U7.B55 (3A_B_IO34_IOB_CLK_B_3A_0p_DIFF_IO_3A_B7p); also elsewhere on the board
GND: R23.2, R248.1; also elsewhere on the board

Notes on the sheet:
SWIZZLING ON BANK 3A (as routed; Quartus varA_routed passes, see LPDDR4_SWIZZLE_PLAN.md) BYTE_SWIZZLE_CH0=1 0 X X X X 3 2; PIN_SWIZZLE_CH0_DQS0 = 5 6 7 0 3 2 1 4; PIN_SWIZZLE_CH0_DQS1 = 10 8 13 14 12 11 9 15; PIN_SWIZZLE_CH0_DQS2 = 20 19 21 18 22 17 23 16; PIN_SWIZZLE_CH0_DQS3 = 27 26 29 28 31 30 2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
LPDDR4 settings (Quartus 26.1.1 / 26.3, emif_io96b_hps 5.0.0 / 5.1.0, tested): 1600 MT/s (800 MHz), refclk 100 MHz from U9 (LVDS) 2133 MT/s also allowed on -6S with the 100 MHz refclk

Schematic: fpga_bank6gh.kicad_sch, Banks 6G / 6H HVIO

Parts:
U7: A5EB013B-B23B; Altera_B23B

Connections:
/clk100: U7.AE11 (6G_IO_HVIO_6G_9_PLLREFCLK1_TXCLK9_RXCLK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); also elsewhere on the board
/fpga_bank6gh/iob6g5: U7.AE8 (6G_IO_HVIO_6G_12_SOURCE_SYNC_CLK2_TXCLK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); also elsewhere on the board
/fpga_bank6gh/iob6h0: U7.BL2 (6H_IO_HVIO_6H_1_TXCLK1_Data_Ctrl1); also elsewhere on the board
/fpga_bank6gh/iob6h1: U7.BL1 (6H_IO_HVIO_6H_2_TXCLK2_Data_Ctrl2); also elsewhere on the board
/fpga_bank6gh/iob6h3: U7.BG2 (6H_IO_HVIO_6H_4_TXCLK4_Data_Ctrl4); also elsewhere on the board
/fpga_bank6gh/iob6h4: U7.BD1 (6H_IO_HVIO_6H_6_TXCLK6_Data_Ctrl6); also elsewhere on the board
/fpga_bank6gh/iob6h5: U7.BD2 (6H_IO_HVIO_6H_5_TXCLK5_Data_Ctrl5); also elsewhere on the board
/fpga_bank6gh/iob6h7: U7.BA1 (6H_IO_HVIO_6H_8_TXCLK8_Data_Ctrl8); also elsewhere on the board
/fpga_bank6gh/iob6h10: U7.AU1 (6H_IO_HVIO_6H_10_PLLREFCLK2_TXCLK10_RXC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); also elsewhere on the board
/fpga_bank6gh/iob6h11: U7.AU2 (6H_IO_HVIO_6H_9_PLLREFCLK1_TXCLK9_RXCLK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); also elsewhere on the board
/fpga_bank6gh/iob6h12: U7.AP1 (6H_IO_HVIO_6H_11_SOURCE_SYNC_CLK1_TXCLK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); also elsewhere on the board
/fpga_bank6gh/iob6h13: U7.AP2 (6H_IO_HVIO_6H_12_SOURCE_SYNC_CLK2_TXCLK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); also elsewhere on the board
/fpga_bank6gh/iob6h14: U7.AM2 (6H_IO_HVIO_6H_13_TXCLK13_Data_Ctrl13); also elsewhere on the board
/fpga_bank6gh/iob6h15: U7.AJ1 (6H_IO_HVIO_6H_16_TXCLK16_Data_Ctrl16); also elsewhere on the board
/fpga_bank6gh/iob6h16: U7.AJ2 (6H_IO_HVIO_6H_15_TXCLK15_Data_Ctrl15); also elsewhere on the board
/fpga_bank6gh/iob6h17: U7.AF1 (6H_IO_HVIO_6H_18_TXCLK18_Data_Ctrl18); also elsewhere on the board
/fpga_bank6gh/iob6h18: U7.AC2 (6H_IO_HVIO_6H_19_TXCLK19_Data_Ctrl19); also elsewhere on the board
/fpga_bank6gh/iob6h19: U7.AC1 (6H_IO_HVIO_6H_20_TXCLK20_Data_Ctrl20); also elsewhere on the board

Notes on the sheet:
VCCIO_6G : 3V3

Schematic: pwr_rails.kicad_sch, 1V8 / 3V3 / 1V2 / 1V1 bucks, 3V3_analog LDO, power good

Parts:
C10: 1u; C_0603_1608Metric; LCSC C15849
C116, C117, C118, C119: 33p; C_0402_1005Metric; LCSC C1562
C157, C158, C159, C160, C161, C163, C164, C165, C167, C169, C203, C204, C205: 22U 6V3; C_0402_1005Metric; LCSC C415703
C162: 100N; C_0402_1005Metric; LCSC C1525
L2, L3, L4, L5: 1u; L_Cenker_CKCS201610; LCSC C97002
R65: 47K; R_0402_1005Metric; LCSC C25792
R80: 100k 0.1%; R_0402_1005Metric; LCSC C852472
R81, R84, R87, R90: DNP; R_0402_1005Metric; not fitted
R82, R85, R91: 200k 0.1%; R_0402_1005Metric; LCSC C728556
R83: 44.2k 0.1%; R_0402_1005Metric; LCSC C705633
R86, R88: 200k; R_0402_1005Metric; LCSC C25764
R89: 240k 0.1%; R_0402_1005Metric; LCSC C852659
R249: 10K; R_0402_1005Metric; LCSC C25744
U6: NCP163ASN330T1G; SOT-23-5; LCSC C603656
U8, U16, U18, U19: AP61203Z6; SOT-563; LCSC C5244557

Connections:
1V1: C119.2, C164.1, C165.1, L5.2, R91.2; also elsewhere on the board
1V2: C118.2, C167.1, C169.1, C203.1, C204.1, C205.1, L4.2, R88.2; also elsewhere on the board
1V8: C116.2, C159.1, L3.2, R65.2, R82.2, R249.1; also elsewhere on the board
3V3: C117.2, C163.1, L2.2, R85.2; also elsewhere on the board
3V3_analog: U6.5 (VOUT); also elsewhere on the board
5V0: C10.1, C157.1, C158.1, C160.1, C161.1, C162.1, U6.1 (VIN), U6.3 (EN), U8.3 (VIN), U16.3 (VIN), U18.3 (VIN), U19.3 (VIN); also elsewhere on the board
/pg_all: R249.2, U8.6 (PG), U16.6 (PG), U19.6 (PG); also elsewhere on the board
/pwr_rails/EN: U18.5 (EN); also elsewhere on the board
GND: C10.2, C157.2, C158.2, C159.2, C160.2, C161.2, C162.2, C163.2, C164.2, C165.2, C167.2, C169.2, C203.2, C204.2, C205.2, R80.2, R81.2, R83.2, R84.2, R86.2, R87.2, R89.2, R90.2, U6.2 (GND), U8.2 (GND), U16.2 (GND), U18.2 (GND), U19.2 (GND); also elsewhere on the board
unnamed: C117.1, R83.1, R84.1, R85.1, U8.1 (FB)
unnamed: L2.1, U8.4 (SW)
unnamed: R65.1, U8.5 (EN), U16.5 (EN), U18.6 (PG), U19.5 (EN)
unnamed: C119.1, R89.1, R90.1, R91.1, U16.1 (FB)
unnamed: L5.1, U16.4 (SW)
unnamed: C116.1, R80.1, R81.1, R82.1, U18.1 (FB)
unnamed: L3.1, U18.4 (SW)
unnamed: C118.1, R86.1, R87.1, R88.1, U19.1 (FB)
unnamed: L4.1, U19.4 (SW)

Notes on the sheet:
PWR_FLAG: rails from regulator / connector pins not typed power output
PG of 1V2 / 3V3 / 1V1 regulators (open drain) wired-AND, 1.8 V level -> U42 ch4 on root -> powergood 3.3 V + LED D1
